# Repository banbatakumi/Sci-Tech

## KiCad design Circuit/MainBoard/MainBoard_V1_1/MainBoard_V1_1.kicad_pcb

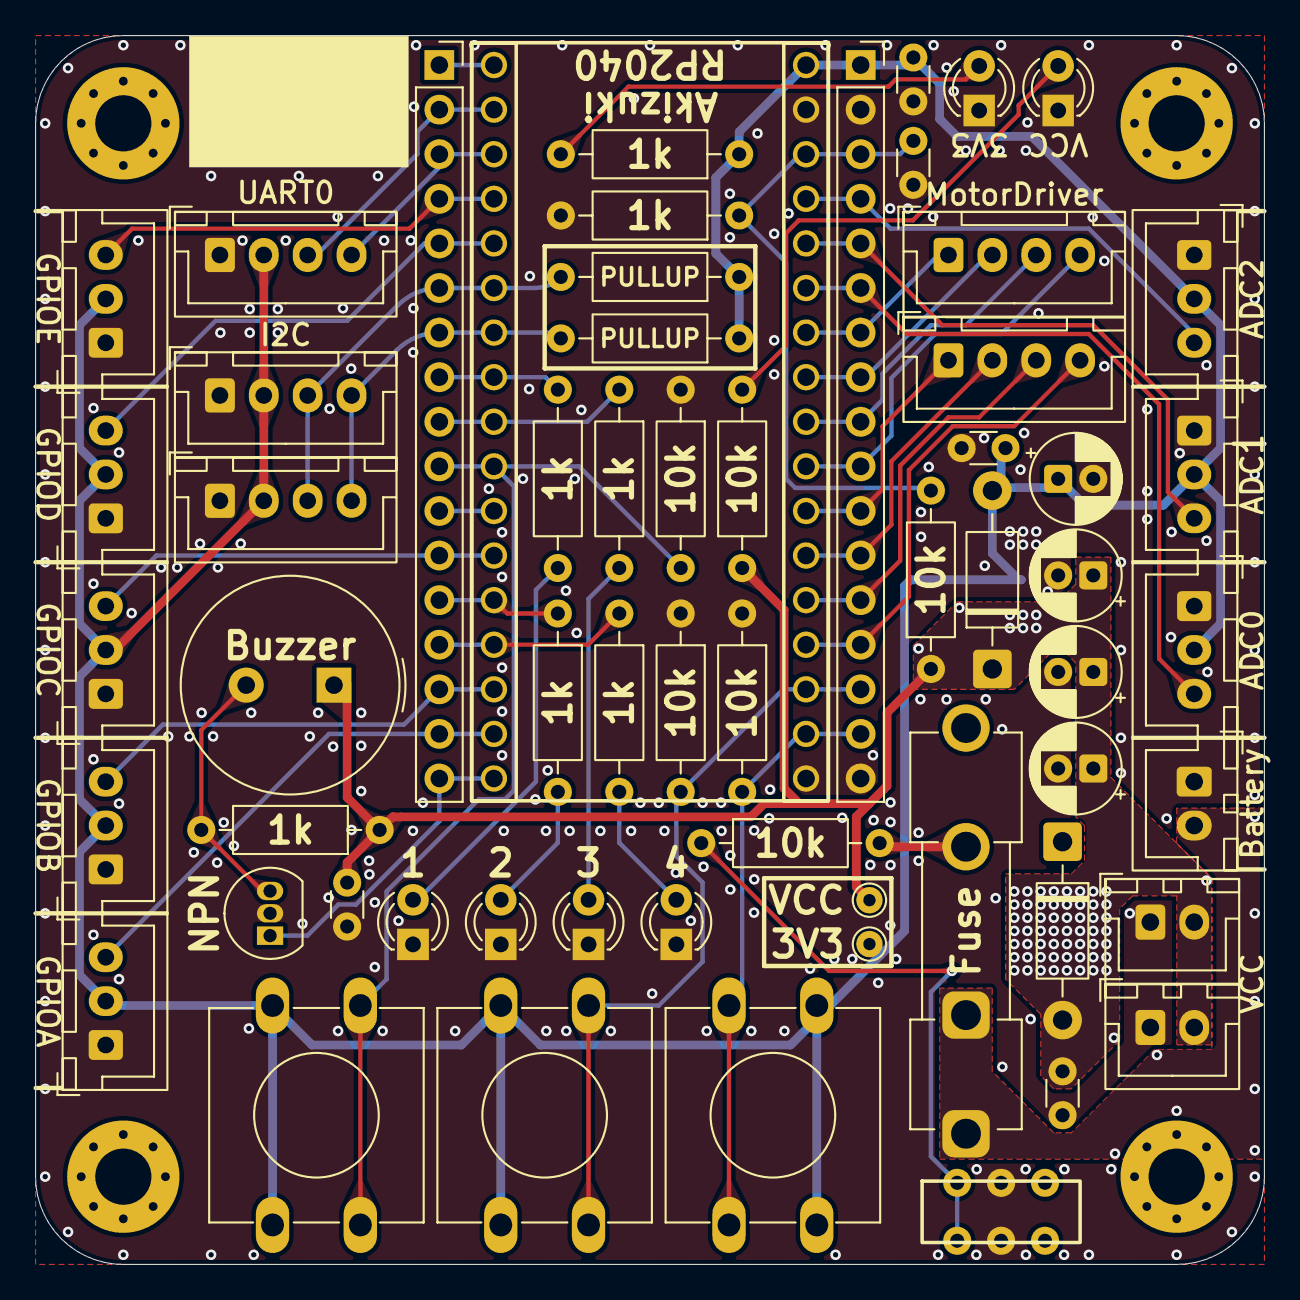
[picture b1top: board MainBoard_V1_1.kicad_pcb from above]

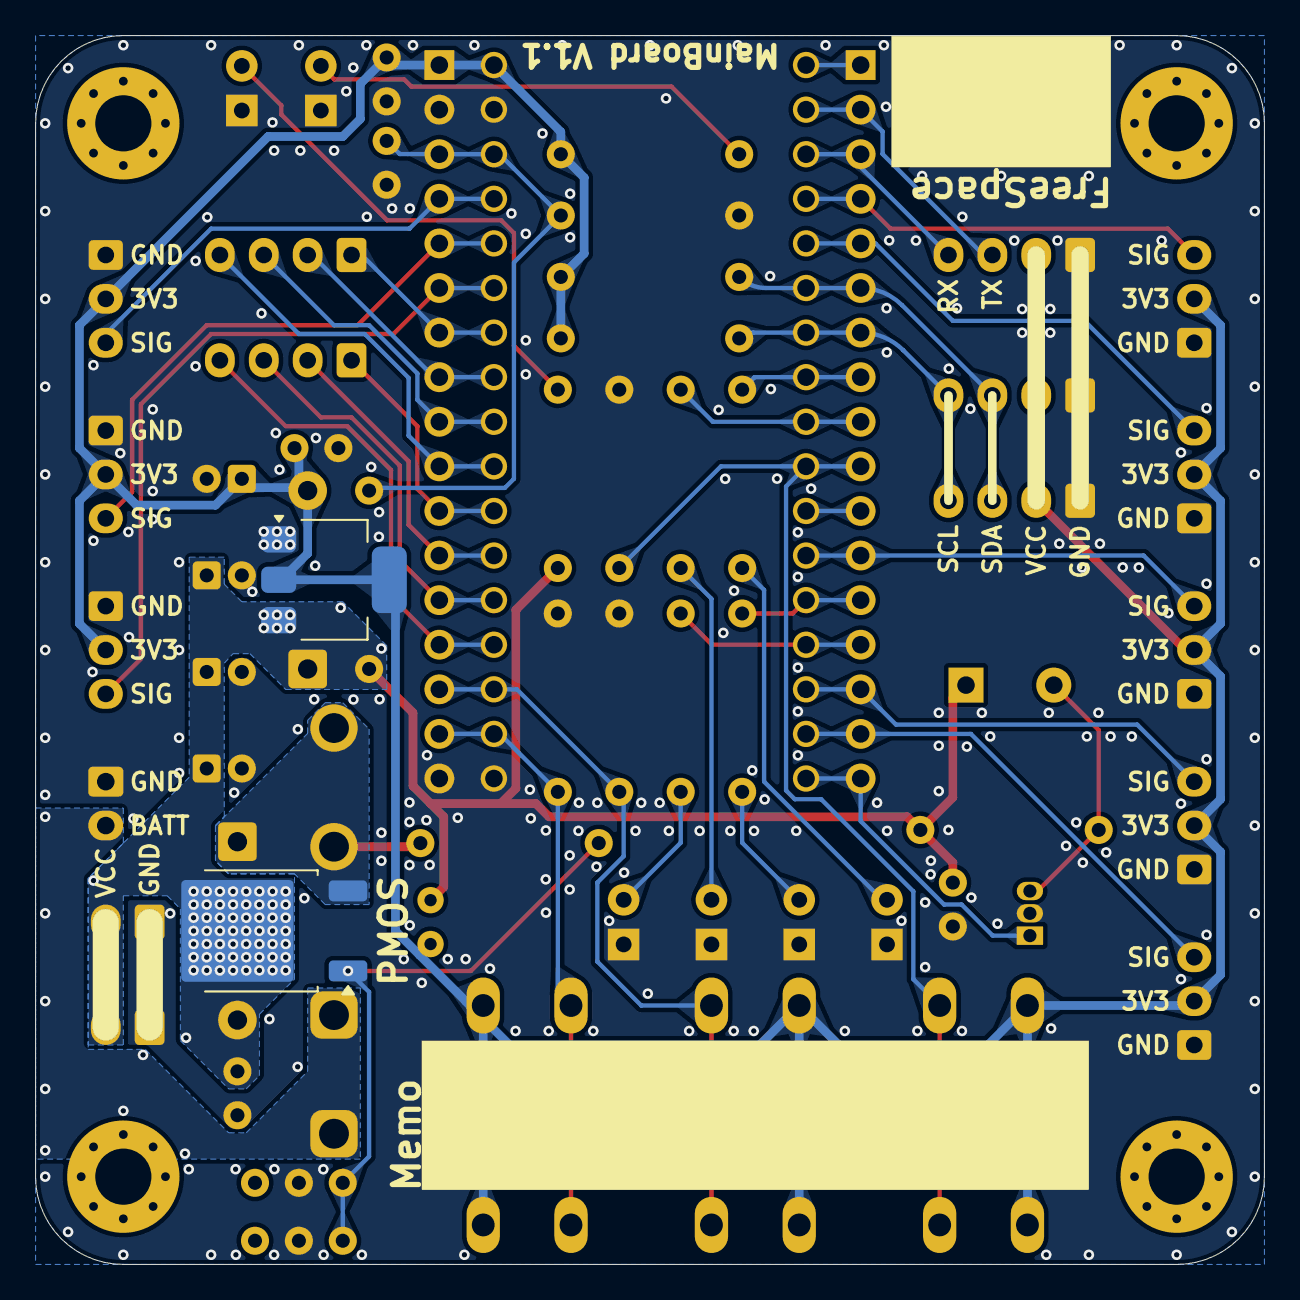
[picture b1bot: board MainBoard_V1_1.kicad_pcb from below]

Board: 2 copper layers, 70.0 x 70.0 mm, 66 parts (2 on the bottom side), 43 nets.

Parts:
BZ1: PKM13EPYH4000-A0; Buzzer_TDK_PS1240P02BT_D12.2mm_H6.5mm
C1, C4: 22uf; CP_Radial_D5.0mm_P2.00mm
C2, C3, C5, C7, C9: 0.1u; C_Disc_D3.0mm_W1.6mm_P2.50mm
C6, C8: 100u; CP_Radial_D5.0mm_P2.00mm
D1, D4, D5, D6, D7, D8: LED; LED_D3.0mm
D2, D3: 1N5819; D_DO-41_SOD81_P10.16mm_Horizontal
F1: 10A; Fuseholder_Clip-5x20mm_Keystone_3517_Inline_P23.11x6.76mm_D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
H1, H2, H3, H4: MountingHole; MountingHole_3.2mm_M3_Pad_Via
J1, J2: Conn_01x17_Socket; PinSocket_1x17_P2.54mm_Vertical
J3, J4, J5: Conn_01x02; JST_XH_B2B-XH-A_1x02_P2.50mm_Vertical
J6, J7, J8, J9, J10: Conn_01x04; JST_XH_B4B-XH-A_1x04_P2.50mm_Vertical
J11, J12, J13, J14, J15, J16, J17, J18: Conn_01x03; JST_XH_B3B-XH-A_1x03_P2.50mm_Vertical
Q1: TJ60S04M3L; TO-252-2
Q2: DTC114E; TO-92_Inline
R1, R4, R6, R7, R9, R11, R12, R15: 1k; R_Axial_DIN0207_L6.3mm_D2.5mm_P10.16mm_Horizontal
R2, R3, R5, R8, R10, R13, R14: 10k; R_Axial_DIN0207_L6.3mm_D2.5mm_P10.16mm_Horizontal
SW1, SW3, SW4: TVGP01-G73BB; SW_PUSH-12mm
SW2: IS-2235
TP1, TP2: TestPoint; TestPoint_THTPad_D1.5mm_Drill0.7mm
U1: LM1117MP-3.3; SOT-223-3_TabPin2
U2: RP2040; RP2040_akitsuki

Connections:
+3V3: C2.2, C3.2, C4.1, D2.2 (A), J2.1, J6.2, J7.2, J8.2, J11.2, J12.2, J13.2, J14.2, J15.2, J16.2, J17.2, J18.2, R12.1, R13.1, R14.1, SW1.1, SW3.1, SW4.1, TP2.1, U1.2 (VO), U2.34 (3.3V)
+BATT: F1.1, J3.2
ADC0: J2.6, J11.3, U2.29 (26)
ADC1: J2.5, J12.3, U2.30 (27)
ADC2: J2.4, J13.3, U2.31 (28)
ADC3: C7.1, J2.3, R8.2, R9.1, U2.32 (29)
BUZZER: J1.17, Q2.1 (B), U2.17 (15)
GND: C1.2, C2.1, C3.1, C4.2, C5.1, C6.2, C7.2, C8.2, C9.1, D1.1 (K), D4.1 (K), D5.1 (K), D6.1 (K), D7.1 (K), D8.1 (K), J2.2, J2.17, J3.1, J4.1, J5.1, J6.1, J7.1, J8.1, J11.1, J12.1, J13.1, J14.1, J15.1, J16.1, J17.1, J18.1, Q2.2 (E), R2.1, R5.1, R9.2, R10.1, SW2.2 (B), SW2.5 (B), U1.1 (GND), U2.18 (GND), U2.33 (GND)
GPIOA: J1.16, J14.3, U2.16 (14)
GPIOB: J1.15, J15.3, U2.15 (13)
GPIOC: J1.12, J16.3, U2.12 (10)
GPIOD: J1.5, J17.3, U2.5 (3)
GPIOE: J1.4, J18.3, U2.4 (2)
LED1: J1.8, R1.1, U2.8 (6)
LED2: J1.13, R4.1, U2.13 (11)
LED3: J1.9, R6.1, U2.9 (7)
LED4: J1.14, R11.1, U2.14 (12)
M1A: J2.7, J9.1, U2.28 (25)
M1B: J2.8, J9.2, U2.27 (24)
M2A: J2.9, J9.3, U2.26 (23)
M2B: J2.10, J9.4, U2.25 (22)
M3A: J2.11, J10.1, U2.24 (21)
M3B: J2.12, J10.2, U2.23 (20)
M4A: J2.13, J10.3, U2.22 (19)
M4B: J2.14, J10.4, U2.21 (18)
unnamed: BZ1.2 (-), Q2.3 (C), R15.2
unnamed: D1.2 (A), R1.2
unnamed: D3.1 (K), F1.2, Q1.3 (S), R3.2
unnamed: D4.2 (A), R4.2
unnamed: D5.2 (A), R6.2
unnamed: D6.2 (A), R7.2
unnamed: D7.2 (A), R11.2
unnamed: D8.2 (A), R12.2
unnamed: J1.11, U2.11 (9)
unnamed: Q1.1 (G), R3.1, SW2.1 (A), SW2.6 (C)
SCL: J1.7, J7.4, J8.4, R14.2, U2.7 (5)
SDA: J1.6, J7.3, J8.3, R13.2, U2.6 (4)
SW1: J1.10, R2.2, SW1.2, U2.10 (8)
SW2: J2.15, R5.2, SW3.2, U2.20 (17)
SW3: J2.16, R10.2, SW4.2, U2.19 (16)
UART0_RX: J1.3, J6.4, U2.3 (1)
UART0_TX: J1.2, J6.3, U2.2 (0)
VCC: BZ1.1 (+), C1.1, C5.2, C6.1, C8.1, C9.2, D2.1 (K), D3.2 (A), J4.2, J5.2, Q1.2 (D), R7.1, R8.1, R15.1, TP1.1, U1.3 (VI)

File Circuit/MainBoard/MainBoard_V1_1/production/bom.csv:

Designator,Footprint,Quantity,Value,LCSC Part #
"_15, _14, _13, _12, _11, _10, _9, _8, _7, _6, _5, _4, _3, _2, ",,15,,
BZ1,Buzzer_TDK_PS1240P02BT_D12.2mm_H6.5mm,1,Buzzer,
"C1, C4",CP_Radial_D5.0mm_P2.00mm,2,22uf,
"C2, C3, C5, C7, C9",C_Disc_D3.0mm_W1.6mm_P2.50mm,5,0.1u,
"C6, C8",CP_Radial_D5.0mm_P2.00mm,2,100u,
"D1, D4, D5, D6, D7, D8",LED_D3.0mm,6,LED,
"D2, D3",D_DO-41_SOD81_P10.16mm_Horizontal,2,1N5819,
F1,Fuseholder_Clip-5x20mm_Keystone_3517_Inline_P23.11x6.76mm_D1.70mm_Horizontal,1,10A,
"J1, J2",PinSocket_1x17_P2.54mm_Vertical,2,Conn_01x17_Socket,
"J10, J6, J7, J8, J9",JST_XH_B4B-XH-A_1x04_P2.50mm_Vertical,5,Conn_01x04,
"J11, J12, J13, J14, J15, J16, J17, J18",JST_XH_B3B-XH-A_1x03_P2.50mm_Vertical,8,Conn_01x03,
"J3, J4, J5",JST_XH_B2B-XH-A_1x02_P2.50mm_Vertical,3,Conn_01x02,
Q1,TO-252-2,1,Q_PMOS_GDS,
Q2,TO-92_Inline,1,DTC114E,
"R1, R11, R15, R4, R6, R9",R_Axial_DIN0207_L6.3mm_D2.5mm_P10.16mm_Horizontal,6,1k,
"R10, R12, R13, R14, R2, R3, R5, R7, R8",R_Axial_DIN0207_L6.3mm_D2.5mm_P10.16mm_Horizontal,9,10k,
"SW1, SW3, SW4",SW_PUSH-12mm,3,SW_Push_Dual,
SW2,IS-2235,1,SW_Slide_DPDT,
"TP1, TP2",TestPoint_THTPad_D1.5mm_Drill0.7mm,2,TestPoint,
U1,SOT-223-3_TabPin2,1,LM1117MP-3.3,
U2,RP2040_akitsuki,1,RP2040,

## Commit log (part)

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2026-05-30 Add .gitignore file for KiCad and OS files
2026-05-30 共通ライブラリの追加
2026-05-30 MD完成
